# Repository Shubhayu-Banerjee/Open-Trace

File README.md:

# OpenTrace

OpenTrace is a custom RP2040-based USB logic analyzer designed to capture digital signals from external circuits for inspection on a computer. This repository documents the hardware design completed so far.

## What has been designed

### RP2040 core

- Selected the **Raspberry Pi RP2040** as the main MCU.
- Designed the core around an external **W25Q16JV QSPI flash** (16 Mbit / 2 MB).
- Added the 12 MHz crystal oscillator circuit, using the RP2040 reference topology as the design basis.
- Added local supply decoupling capacitors and the RP2040's 3.3 V / 1.1 V regulator-related connections.
- Tied `TESTEN` low.
- Added a `RUN` reset circuit using a 10 kΩ pull-up to +3V3 and a normally-open momentary switch to GND.

### USB-C interface

- Added a USB-C receptacle for USB 2.0 device connectivity.
- Added separate **5.1 kΩ pull-down resistors from CC1 and CC2 to GND**.
- Combined the receptacle's duplicate USB 2.0 contacts correctly: A6/B6 for D+ and A7/B7 for D−.
- Added a **USBLC6-2SC6** for USB D+/D− ESD protection.
- Added an **AMS1117-3.3** regulator stage to derive 3.3 V from USB VBUS in the current schematic.

### Eight-channel input stage

- Selected the **SN74LVC245A-family octal buffer**, with the current schematic using `SN74LVC245APW`.
- Set `DIR` low for A-to-B signal flow.
- Set active-low `/OE` low to enable the outputs.
- Added a 100 nF bypass capacitor at the buffer's supply.
- Added an eight-signal probe connector (`J2`) and wired its eight signals to buffer inputs A1–A8.
- Wired the corresponding B1–B8 outputs to RP2040 GPIOs **GPIO25 through GPIO18**, respectively:

| Probe / buffer channel | RP2040 GPIO |
|---|---:|
| Channel 1 (A1 → B1) | GPIO18 |
| Channel 2 (A2 → B2) | GPIO19 |
| Channel 3 (A3 → B3) | GPIO20 |
| Channel 4 (A4 → B4) | GPIO21 |
| Channel 5 (A5 → B5) | GPIO22 |
| Channel 6 (A6 → B6) | GPIO23 |
| Channel 7 (A7 → B7) | GPIO24 |
| Channel 8 (A8 → B8) | GPIO25 |

The mapping above records the schematic mapping discussed so far; it must still be checked against the final display/encoder pin assignments.

### Probe-input ESD decision

- Evaluated multiple eight-channel and single-/multi-line ESD protection options, including the SP4065-08ATG, TPD4E05U06, DRTR5V0U4S-7, PESD5V0U1BA, PESD5V0L1BA, NUP4114, and PESD5V0C2BDFZ.
- No probe-side ESD protector was selected as a verified solution. The main blocker was finding a part that was available, had a practical footprint, and had transient/clamping characteristics appropriately evaluated against the SN74LVC245A input limits.
- **The current design decision is to omit the dedicated probe-input ESD array for this revision**, rather than add an unverified component. This leaves the exposed probe inputs without dedicated ESD protection and is a known limitation.
- The USBLC6-2SC6 remains assigned to USB D+/D−, not to the probe inputs.

## Important current design details

| Item | Current design |
|---|---|
| Main MCU | Raspberry Pi RP2040 |
| QSPI flash | W25Q16JV, 16 Mbit / 2 MB |
| Clock | 12 MHz crystal circuit |
| USB | USB-C, USB 2.0 |
| USB ESD | USBLC6-2SC6 on D+/D− |
| USB-to-3.3 V regulator | AMS1117-3.3 candidate |
| Probe buffer | SN74LVC245APW |
| Probe inputs | 8 digital channels |
| Probe-to-GPIO mapping | GPIO25, GPIO24, GPIO23, GPIO22, GPIO21, GPIO20, GPIO19, GPIO18 |
| Probe ESD | Omitted for current revision; not protected by a dedicated ESD array |
| Reset | `RUN` with 10 kΩ pull-up and momentary switch to GND |
| Boot configuration | `TESTEN` tied low; flash/BOOTSEL arrangement needs final verification |

## Decisions and trade-offs made

- Chose **RP2040** rather than a more complex FPGA or another MCU for this revision, prioritizing a feasible custom board and PIO-based deterministic sampling.
- Kept the external QSPI flash and 12 MHz crystal as part of the bare-MCU design.
- Used a USB-C connector with the correct device-side CC pull-down approach.
- Added dedicated ESD protection to the USB data lines.
- Chose the SN74LVC245A-family device as the eight-channel input buffer.
- Deferred probe-input ESD protection because candidate parts were unavailable or could not be validated as a complete protection solution within the current design effort.
- Prioritized getting a coherent, manufacturable first PCB over adding a component whose electrical suitability was uncertain.

## Known limitations / items not yet verified

This repository describes the design work completed so far; it does not claim the PCB has been fabricated or tested.
- The probe inputs have no dedicated ESD array in the current revision. Treat them as unprotected inputs.

## References

- [RP2040 hardware design guide](https://datasheets.raspberrypi.com/rp2040/hardware_design_with_rp2040.pdf)
- [RP2040 documentation portal](https://pip.raspberrypi.com/categories/814-rp2040)
- [Texas Instruments SN74LVC245A](https://www.ti.com/product/SN74LVC245A)
- [ST USBLC6-2SC6](https://www.st.com/en/protections-and-emi-filters/usbllc6-2.html)

## BOM

| Reference | Qty | Value | DNP | Exclude from BOM | Exclude from Board | Footprint | Datasheet |
|---|---:|---|---|---|---|---|---|
| C1,C3,C4,C6,C7,C8,C9,C10,C11,C17,C18 | 11 | 100nF | | | | `Capacitor_SMD:C_0603_1608Metric` | |
| C5,C12,C15,C16 | 4 | 1 µF | | | | `Capacitor_SMD:C_0603_1608Metric` | |
| C13,C14 | 2 | 15p | | | | `Capacitor_SMD:C_0603_1608Metric` | |
| D1 | 1 | LED | | | | `LED_SMD:LED_0805_2012Metric` | |
| J1 | 1 | USB_C_Receptacle_USB2.0_16P | | | | `Connector_USB:USB_C_Receptacle_GCT_USB4105-xx-A_16P_TopMnt_Horizontal` | [USB Type-C Specification](https://www.usb.org/sites/default/files/documents/usb_type-c.zip) |
| J2 | 1 | Conn_01x16_Pin | | | | `Connector_PinHeader_2.54mm:PinHeader_1x16_P2.54mm_Vertical` | |
| R1,R2,R6 | 3 | 1k | | | | `Resistor_SMD:R_0603_1608Metric` | |
| R3 | 1 | 10k | | | | `Resistor_SMD:R_0603_1608Metric` | |
| R4,R5 | 2 | 5.1k | | | | `Resistor_SMD:R_0603_1608Metric` | |
| SW1 | 1 | Boot_SEL | | | | `Button_Switch_THT:SW_PUSH_6mm` | |
| SW2 | 1 | RUN | | | | `Button_Switch_THT:SW_PUSH_6mm` | |
| U1 | 1 | RP2040 | | | | `Package_DFN_QFN:QFN-56-1EP_7x7mm_P0.4mm_EP3.2x3.2mm` | [RP2040 Datasheet](https://datasheets.raspberrypi.com/rp2040/rp2040-datasheet.pdf) |
| U2 | 1 | SN74LVC245APW | | | | `Package_SO:TSSOP-20_4.4x6.5mm_P0.65mm` | [TI Datasheet](https://www.ti.com/lit/ds/scas218x/scas218x.pdf) |
| U3 | 1 | USBLC6-2SC6 | | | | `Package_TO_SOT_SMD:SOT-23-6` | [ST Datasheet](https://www.st.com/resource/en/datasheet/usblc6-2.pdf) |
| U4 | 1 | W25Q16JVSS | | | | `Package_SO:SOIC-8_5.3x5.3mm_P1.27mm` | [Winbond Documentation](https://www.winbond.com/hq/support/documentation/levelOne.jsp?__locale=en&DocNo=DA00-W25Q16JV.1) |
| U5 | 1 | AMS1117-3.3 | | | | `Package_TO_SOT_SMD:SOT-223-3_TabPin2` | [AMS1117 Datasheet](http://www.advanced-monolithic.com/pdf/ds1117.pdf) |
| Y1 | 1 | Crystal_GND24 | | | | `Crystal:Crystal_SMD_3225-4Pin_3.2x2.5mm` | |

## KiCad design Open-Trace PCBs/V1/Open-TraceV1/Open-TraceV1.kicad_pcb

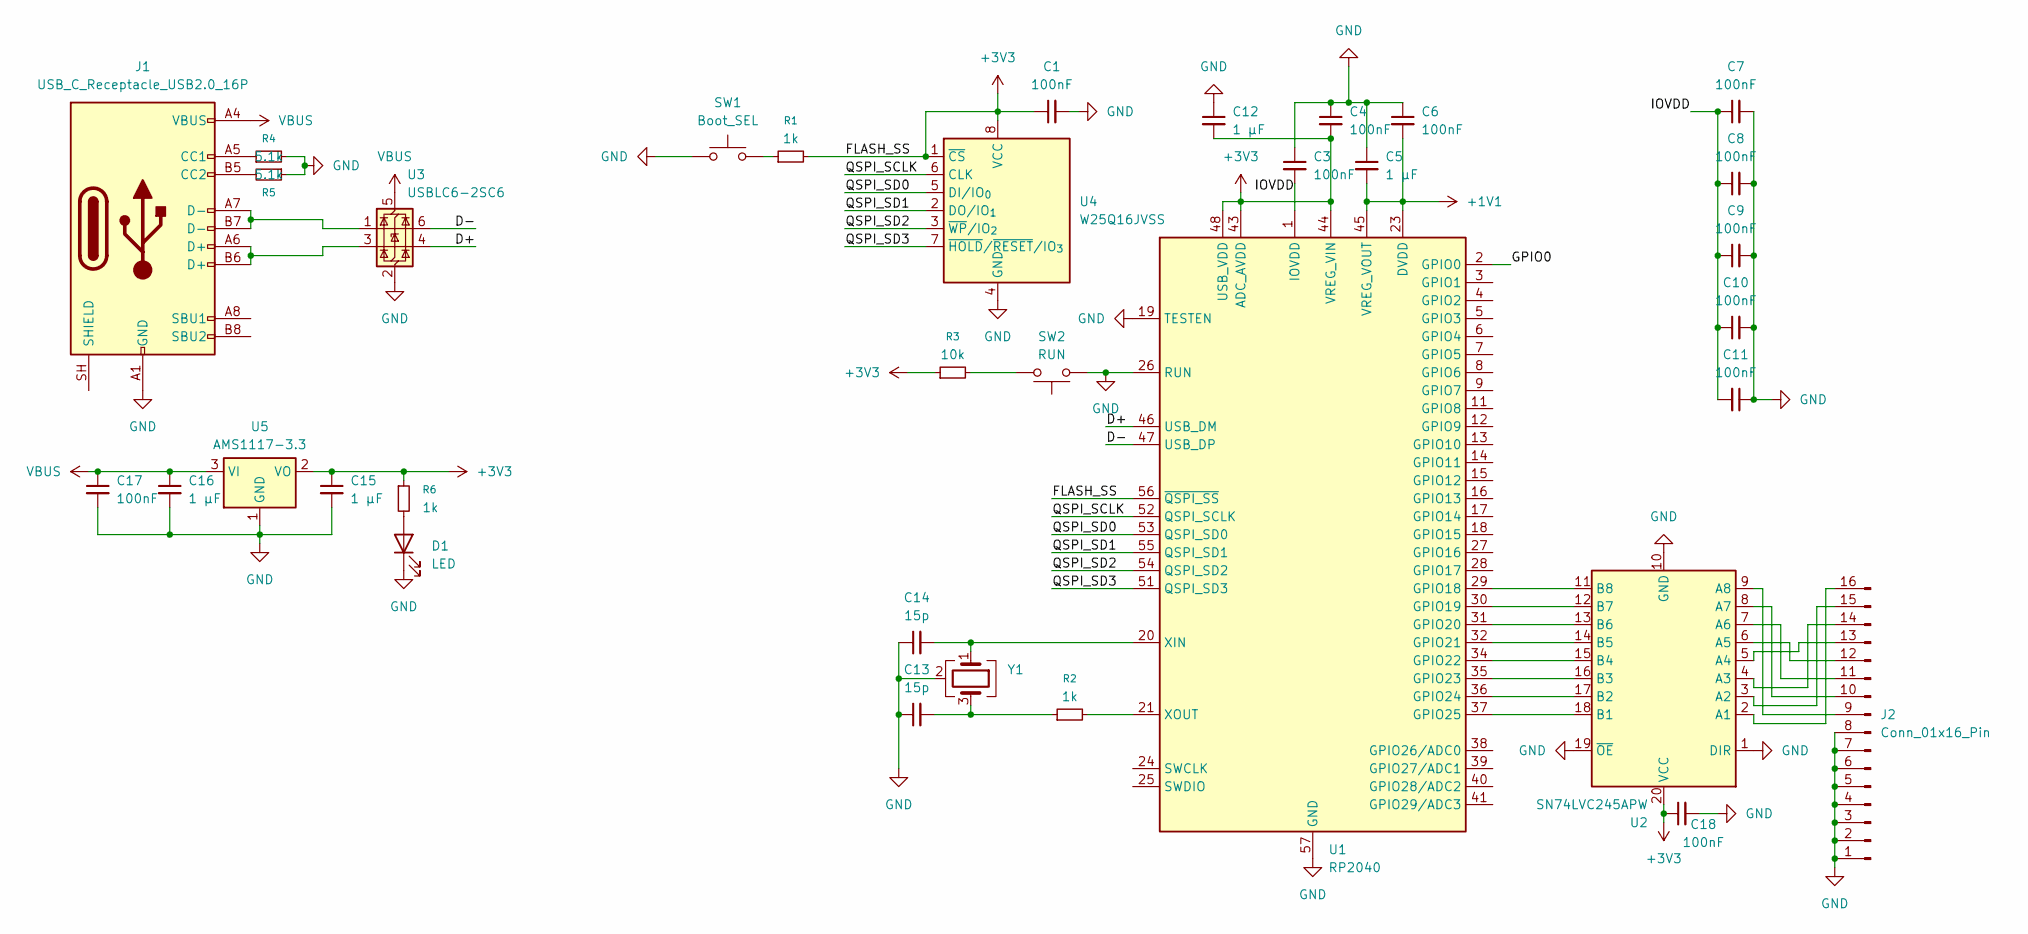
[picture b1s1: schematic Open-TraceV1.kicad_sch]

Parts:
C1, C3, C4, C6, C7, C8, C9, C10, C11, C17, C18: 100nF; C_0603_1608Metric
C5, C12, C15, C16: 1 µF; C_0603_1608Metric
C13, C14: 15p; C_0603_1608Metric
D1: LED; LED_0805_2012Metric
J1: USB_C_Receptacle_USB2.0_16P; USB_C_Receptacle_GCT_USB4105-xx-A_16P_TopMnt_Horizontal
J2: Conn_01x16_Pin; PinHeader_1x16_P2.54mm_Vertical
R1, R2, R6: 1k; R_0603_1608Metric
R3: 10k; R_0603_1608Metric
R4, R5: 5.1k; R_0603_1608Metric
SW1: Boot_SEL; SW_PUSH_6mm
SW2: RUN; SW_PUSH_6mm
U1: RP2040; QFN-56-1EP_7x7mm_P0.4mm_EP3.2x3.2mm
U2: SN74LVC245APW; TSSOP-20_4.4x6.5mm_P0.65mm
U3: USBLC6-2SC6; SOT-23-6
U4: W25Q16JVSS; SOIC-8_5.3x5.3mm_P1.27mm
U5: AMS1117-3.3; SOT-223-3_TabPin2
Y1: Crystal_GND24; Crystal_SMD_3225-4Pin_3.2x2.5mm

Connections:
+1V1: C5.2, C6.2, U1.23 (DVDD), U1.45 (VREG_VOUT), U1.50 (DVDD)
+3V3: C1.1, C4.2, C12.2, C15.1, C18.1, R1.2, R3.1, R6.1, U1.43 (ADC_AVDD), U1.44 (VREG_VIN), U1.48 (USB_VDD), U1.56 (~QSPI_SS), U2.20 (VCC), U4.1 (~CS), U4.8 (VCC), U5.2 (VO)
/D+: U1.46 (USB_DM), U3.4 (I/O2)
/D-: U1.47 (USB_DP), U3.6 (I/O1)
/GPIO0: U1.2 (GPIO0)
/IOVDD: C3.2, C7.1, C8.1, C9.1, C10.1, C11.2, U1.1 (IOVDD), U1.10 (IOVDD), U1.22 (IOVDD), U1.33 (IOVDD), U1.42 (IOVDD), U1.49 (IOVDD)
/QSPI_SCLK: U1.52 (QSPI_SCLK), U4.6 (CLK)
/QSPI_SD0: U1.53 (QSPI_SD0), U4.5 (DI/IO_{0})
/QSPI_SD1: U1.55 (QSPI_SD1), U4.2 (DO/IO_{1})
/QSPI_SD2: U1.54 (QSPI_SD2), U4.3 (~WP/IO_{2})
/QSPI_SD3: U1.51 (QSPI_SD3), U4.7 (~HOLD/~RESET/IO_{3})
GND: C1.2, C3.1, C4.1, C5.1, C6.1, C7.2, C8.2, C9.2, C10.2, C11.1, C12.1, C13.1, C14.1, C15.2, C16.2, C17.2, C18.2, D1.1 (K), J1.A1 (GND), J1.A12 (GND), J1.B1 (GND), J1.B12 (GND), J2.1, J2.2, J2.3, J2.4, J2.5, J2.6, J2.7, J2.8, R4.2, R5.1, SW1.1, SW2.1, U1.19 (TESTEN), U1.26 (RUN), U1.57 (GND), U2.1 (DIR), U2.10 (GND), U2.19 (~OE), U3.2 (GND), U4.4 (GND), U5.1 (GND), Y1.2 (G), Y1.4 (G)
unnamed: C13.2, R2.1, Y1.3
unnamed: D1.2 (A), R6.2
unnamed: J1.A5 (CC1), R4.1
unnamed: J1.B5 (CC2), R5.2
unnamed: J1.A6 (D+), J1.B6 (D+), U3.3 (I/O2)
unnamed: J1.A7 (D-), J1.B7 (D-), U3.1 (I/O1)
unnamed: J2.9, U2.9 (A8)
unnamed: J2.10, U2.8 (A7)
unnamed: J2.11, U2.7 (A6)
unnamed: J2.12, U2.6 (A5)
unnamed: J2.13, U2.5 (A4)
unnamed: J2.14, U2.4 (A3)
unnamed: J2.15, U2.3 (A2)
unnamed: J2.16, U2.2 (A1)
unnamed: R1.1, SW1.2
unnamed: R3.2, SW2.2
unnamed: U1.29 (GPIO18), U2.11 (B8)
unnamed: U1.30 (GPIO19), U2.12 (B7)
unnamed: U1.31 (GPIO20), U2.13 (B6)
unnamed: U1.32 (GPIO21), U2.14 (B5)
unnamed: U1.34 (GPIO22), U2.15 (B4)
unnamed: U1.35 (GPIO23), U2.16 (B3)
unnamed: U1.36 (GPIO24), U2.17 (B2)
unnamed: U1.37 (GPIO25), U2.18 (B1)
unnamed: C14.2, U1.20 (XIN), Y1.1
unnamed: R2.2, U1.21 (XOUT)
VBUS: C16.1, C17.1, J1.A4 (VBUS), J1.A9 (VBUS), J1.B4 (VBUS), J1.B9 (VBUS), U3.5 (VBUS), U5.3 (VI)

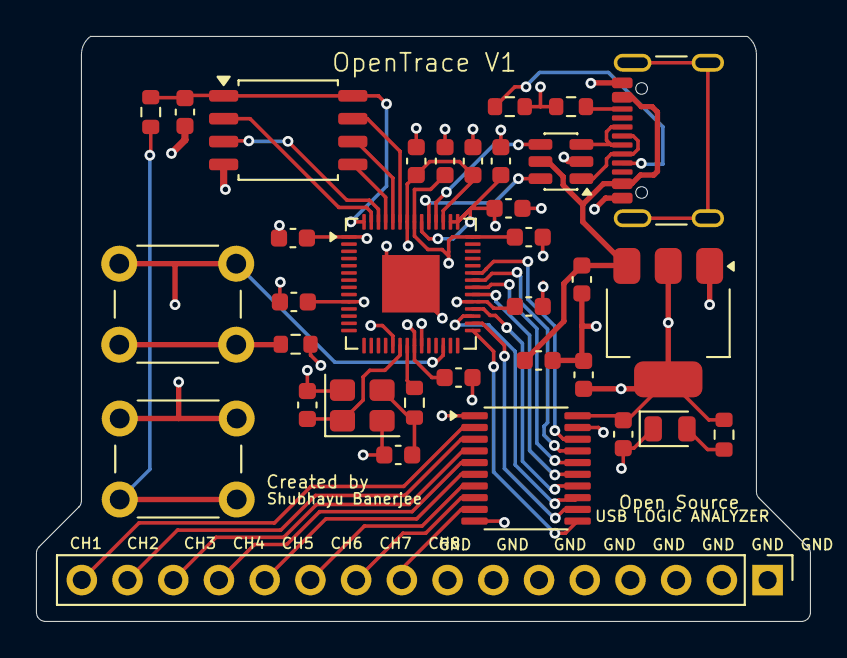
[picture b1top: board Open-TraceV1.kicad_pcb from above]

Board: 4 copper layers, 43.0 x 32.5 mm, 34 parts (0 on the bottom side), 38 nets.

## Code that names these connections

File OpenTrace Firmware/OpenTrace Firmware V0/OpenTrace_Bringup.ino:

/*
  OpenTrace — temporary bring-up firmware
  Target: Raspberry Pi RP2040
  Framework: Arduino-Pico core (Raspberry Pi Pico / RP2040)

  Purpose:
    - Confirm the RP2040 boots and enumerates as USB serial.
    - Confirm the eight SN74LVC245A output channels reach the expected GPIOs.
    - Print a channel bitmask when the input state changes.

  IMPORTANT:
    This is a low-speed GPIO polling test, NOT the final high-speed logic analyzer.
    It does not use PIO/DMA and cannot guarantee narrow-pulse capture.
*/

#include <Arduino.h>

static constexpr uint32_t SERIAL_BAUD = 115200;
static constexpr uint32_t REPORT_INTERVAL_MS = 100;

// Based on the current schematic mapping:
// CH1=A1->B1 -> GPIO25, CH2 -> GPIO24, ... CH8 -> GPIO18.
static constexpr uint8_t CHANNEL_PINS[8] = {
  25, 24, 23, 22, 21, 20, 19, 18
};

uint8_t readChannels() {
  uint8_t state = 0;
  for (uint8_t ch = 0; ch < 8; ++ch) {
    if (digitalRead(CHANNEL_PINS[ch]) == HIGH) {
      state |= (uint8_t)(1u << ch);
    }
  }
  return state;
}

void printState(uint8_t state) {
  Serial.print(F("CH1..CH8 = "));
  for (int8_t ch = 7; ch >= 0; --ch) {
    Serial.print((state >> ch) & 1u);
  }

  Serial.print(F("  HEX=0x"));
  if (state < 0x10) Serial.print('0');
  Serial.println(state, HEX);
}

void setup() {
  // Use INPUT: the SN74LVC245A actively drives these GPIOs.
  for (uint8_t ch = 0; ch < 8; ++ch) {
    pinMode(CHANNEL_PINS[ch], INPUT);
  }

  Serial.begin(SERIAL_BAUD);

  // Don't block indefinitely if no serial terminal is open.
  const uint32_t start = millis();
  while (!Serial && (millis() - start < 3000)) {
    delay(10);
  }

  Serial.println();
  Serial.println(F("OpenTrace temporary bring-up firmware"));
  Serial.println(F("RP2040 USB serial: OK"));
  Serial.println(F("8-channel GPIO polling test"));
  Serial.println(F("Mapping: CH1=GPIO25, CH2=GPIO24, CH3=GPIO23, CH4=GPIO22,"));
  Serial.println(F("         CH5=GPIO21, CH6=GPIO20, CH7=GPIO19, CH8=GPIO18"));
  Serial.println(F("Send 's' to print the current state."));
  Serial.println(F("NOTE: slow polling only; not final logic-analyzer capture."));
  printState(readChannels());
}

void loop() {
  static uint8_t previousState = 0xFF;
  static uint32_t lastReport = 0;

  const uint32_t now = millis();
  const uint8_t state = readChannels();

  // Print immediately whenever any channel changes.
  if (state != previousState) {
    Serial.print(millis());
    Serial.print(F(" ms  "));
    printState(state);
    previousState = state;
    lastReport = now;
  }

  // Allow a terminal to request a fresh state.
  while (Serial.available() > 0) {
    const char command = (char)Serial.read();
    if (command == 's' || command == 'S') {
      Serial.print(millis());
      Serial.print(F(" ms  "));
      printState(state);
    }
  }

  // Periodic heartbeat so the terminal shows the firmware is alive.
  if (now - lastReport >= REPORT_INTERVAL_MS) {
    Serial.print(millis());
    Serial.print(F(" ms  "));
    printState(state);
    lastReport = now;
  }
}
